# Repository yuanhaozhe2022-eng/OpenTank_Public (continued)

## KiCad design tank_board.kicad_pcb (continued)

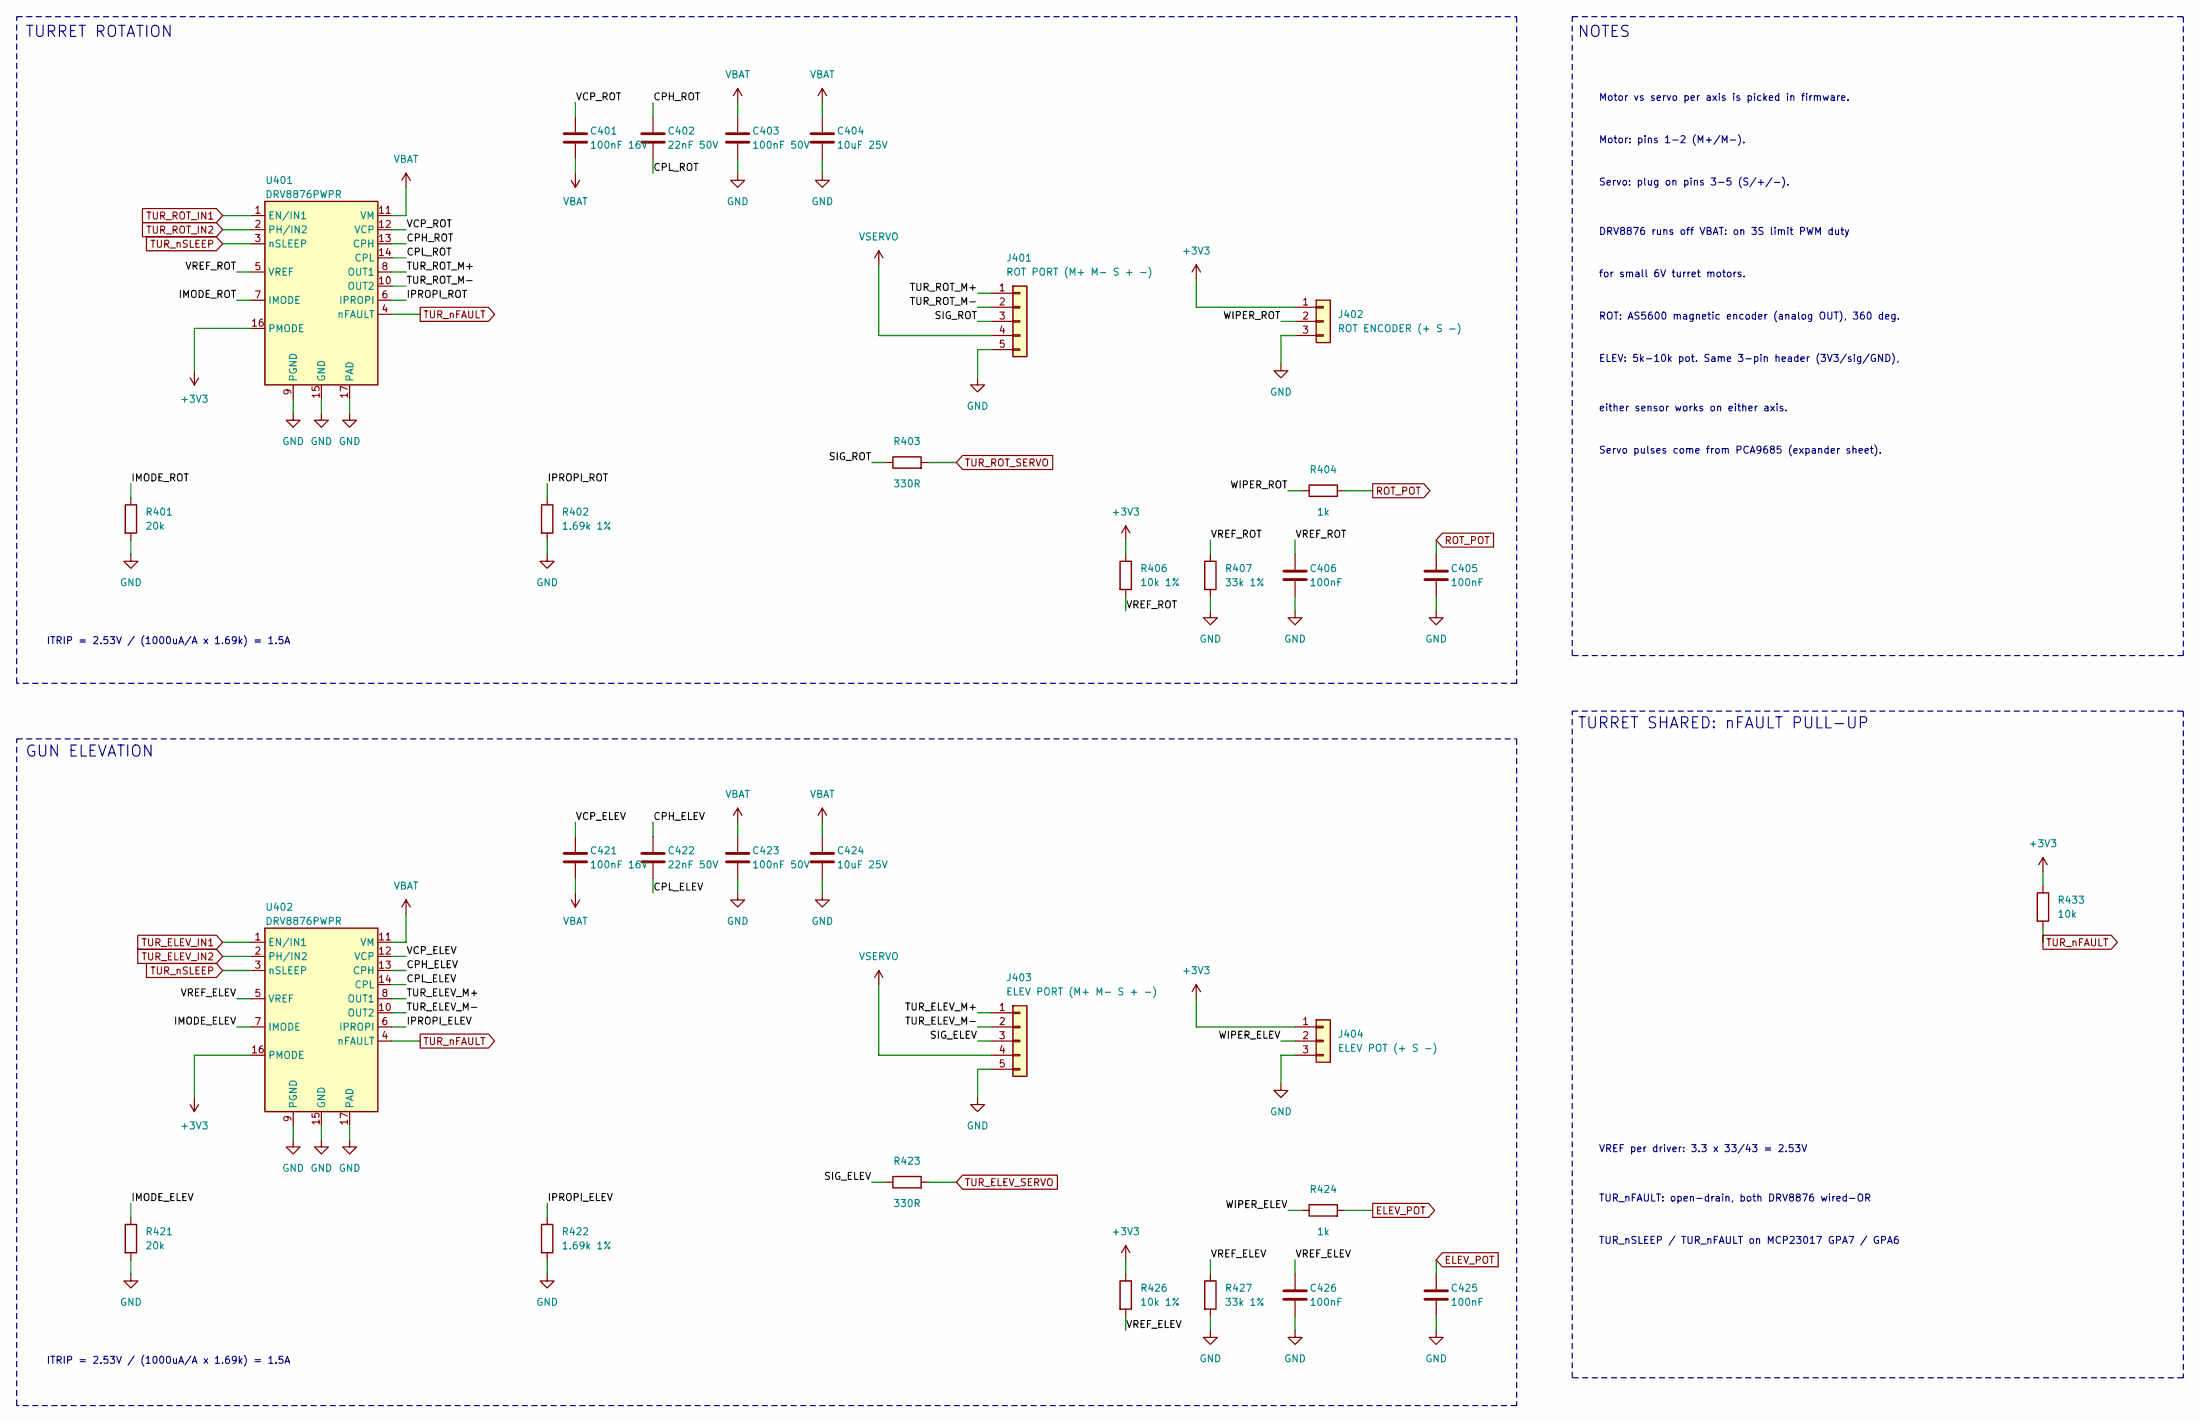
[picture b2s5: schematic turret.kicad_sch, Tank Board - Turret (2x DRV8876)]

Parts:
C401, C421: 100nF 16V; C_0603_1608Metric
C402, C422: 22nF 50V; C_0603_1608Metric
C403, C423: 100nF 50V; C_0603_1608Metric
C404, C424: 10uF 25V; C_1206_3216Metric
C405, C406, C425, C426: 100nF; C_0603_1608Metric
J401: ROT PORT (M+ M- S + -); PinHeader_1x05_P2.54mm_Vertical
J402: ROT ENCODER (+ S -); PinHeader_1x03_P2.54mm_Vertical
J403: ELEV PORT (M+ M- S + -); PinHeader_1x05_P2.54mm_Vertical
J404: ELEV POT (+ S -); PinHeader_1x03_P2.54mm_Vertical
R401, R421: 20k; R_0603_1608Metric
R402, R422: 1.69k 1%; R_0603_1608Metric
R403, R423: 330R; R_0603_1608Metric
R404, R424: 1k; R_0603_1608Metric
R406, R426: 10k 1%; R_0603_1608Metric
R407, R427: 33k 1%; R_0603_1608Metric
R433: 10k; R_0603_1608Metric
U401, U402: DRV8876PWPR; DRV887x_HTSSOP-16_PWP0016J_ThermalVias; MPN DRV8876PWPR

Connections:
+3V3: J402.1, J404.1, R406.1, R426.1, R433.1, U401.16 (PMODE), U402.16 (PMODE); also elsewhere on the board
/Turret/CPH_ELEV: C422.1, U402.13 (CPH)
/Turret/CPH_ROT: C402.1, U401.13 (CPH)
/Turret/CPL_ELEV: C422.2, U402.14 (CPL)
/Turret/CPL_ROT: C402.2, U401.14 (CPL)
/Turret/IMODE_ELEV: R421.1, U402.7 (IMODE)
/Turret/IMODE_ROT: R401.1, U401.7 (IMODE)
/Turret/IPROPI_ELEV: R422.1, U402.6 (IPROPI)
/Turret/IPROPI_ROT: R402.1, U401.6 (IPROPI)
/Turret/SIG_ELEV: J403.3, R423.1
/Turret/SIG_ROT: J401.3, R403.1
/Turret/TUR_ELEV_M+: J403.1, U402.8 (OUT1)
/Turret/TUR_ELEV_M-: J403.2, U402.10 (OUT2)
/Turret/TUR_ROT_M+: J401.1, U401.8 (OUT1)
/Turret/TUR_ROT_M-: J401.2, U401.10 (OUT2)
/Turret/VCP_ELEV: C421.1, U402.12 (VCP)
/Turret/VCP_ROT: C401.1, U401.12 (VCP)
/Turret/VREF_ELEV: C426.1, R426.2, R427.1, U402.5 (VREF)
/Turret/VREF_ROT: C406.1, R406.2, R407.1, U401.5 (VREF)
/Turret/WIPER_ELEV: J404.2, R424.1
/Turret/WIPER_ROT: J402.2, R404.1
ELEV_POT: C425.1, R424.2; also elsewhere on the board
GND: C403.2, C404.2, C405.2, C406.2, C423.2, C424.2, C425.2, C426.2, J401.5, J402.3, J403.5, J404.3, R401.2, R402.2, R407.2, R421.2, R422.2, R427.2, U401.9 (PGND), U401.15 (GND), U401.17 (PAD), U402.9 (PGND), U402.15 (GND), U402.17 (PAD); also elsewhere on the board
ROT_POT: C405.1, R404.2; also elsewhere on the board
TUR_ELEV_IN1: U402.1 (EN/IN1); also elsewhere on the board
TUR_ELEV_IN2: U402.2 (PH/IN2); also elsewhere on the board
TUR_ELEV_SERVO: R423.2; also elsewhere on the board
TUR_ROT_IN1: U401.1 (EN/IN1); also elsewhere on the board
TUR_ROT_IN2: U401.2 (PH/IN2); also elsewhere on the board
TUR_ROT_SERVO: R403.2; also elsewhere on the board
TUR_nFAULT: R433.2, U401.4 (nFAULT), U402.4 (nFAULT); also elsewhere on the board
TUR_nSLEEP: U401.3 (nSLEEP), U402.3 (nSLEEP); also elsewhere on the board
VBAT: C401.2, C403.1, C404.1, C421.2, C423.1, C424.1, U401.11 (VM), U402.11 (VM); also elsewhere on the board
VSERVO: J401.4, J403.4; also elsewhere on the board

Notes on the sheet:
TURRET ROTATION
ITRIP = 2.53V / (1000uA/A x 1.69k) = 1.5A
GUN ELEVATION
TURRET SHARED: nFAULT PULL-UP
VREF per driver: 3.3 x 33/43 = 2.53V
TUR_nFAULT: open-drain, both DRV8876 wired-OR
TUR_nSLEEP / TUR_nFAULT on MCP23017 GPA7 / GPA6
NOTES
Motor vs servo per axis is picked in firmware.
Motor: pins 1-2 (M+/M-).
Servo: plug on pins 3-5 (S/+/-).
DRV8876 runs off VBAT: on 3S limit PWM duty
for small 6V turret motors.
ROT: AS5600 magnetic encoder (analog OUT), 360 deg.
ELEV: 5k-10k pot. Same 3-pin header (3V3/sig/GND),
either sensor works on either axis.
Servo pulses come from PCA9685 (expander sheet).

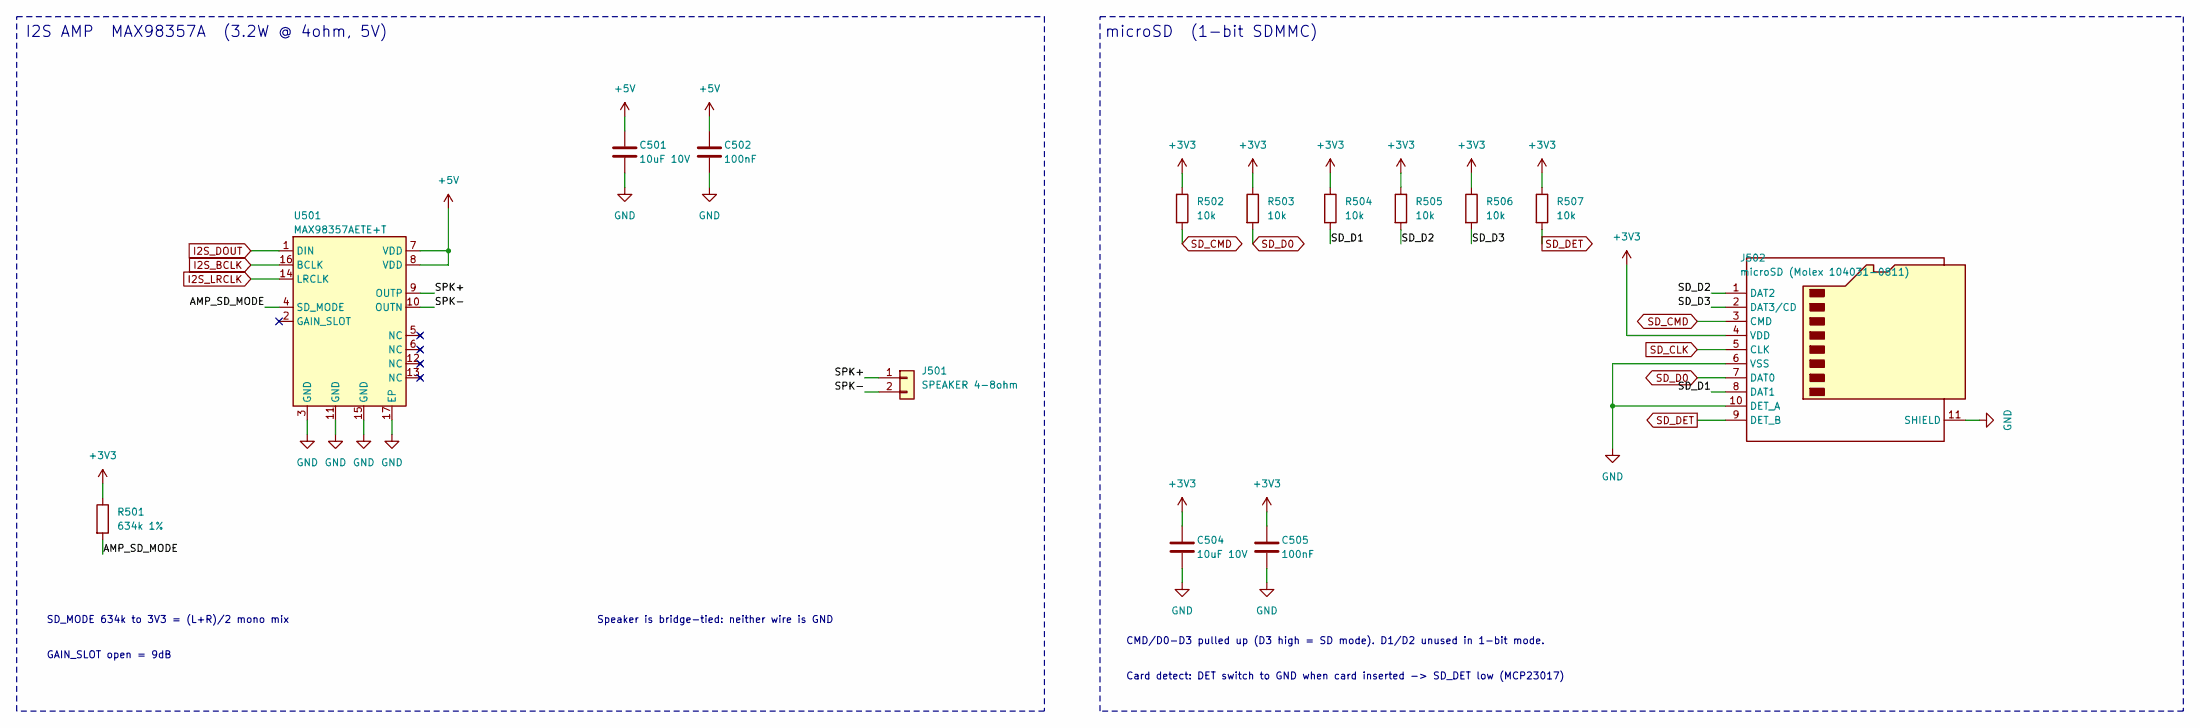
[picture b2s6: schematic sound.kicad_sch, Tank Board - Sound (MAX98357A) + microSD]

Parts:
C501, C504: 10uF 10V; C_0805_2012Metric
C502, C505: 100nF; C_0603_1608Metric
J501: SPEAKER 4-8ohm; JST_PH_B2B-PH-K_1x02_P2.00mm_Vertical; MPN JST B2B-PH-K-S
J502: microSD (Molex 104031-0811); microSD_HC_Molex_104031-0811; MPN Molex 104031-0811
R501: 634k 1%; R_0603_1608Metric
R502, R503, R504, R505, R506, R507: 10k; R_0603_1608Metric
U501: MAX98357AETE+T; TQFN-16-1EP_3x3mm_P0.5mm_EP1.23x1.23mm_ThermalVias; MPN MAX98357AETE+T

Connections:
+3V3: C504.1, C505.1, J502.4 (VDD), R501.1, R502.1, R503.1, R504.1, R505.1, R506.1, R507.1; also elsewhere on the board
+5V: C501.1, C502.1, U501.7 (VDD), U501.8 (VDD); also elsewhere on the board
/Sound_SD/AMP_SD_MODE: R501.2, U501.4 (SD_MODE)
/Sound_SD/SD_D1: J502.8 (DAT1), R504.2
/Sound_SD/SD_D2: J502.1 (DAT2), R505.2
/Sound_SD/SD_D3: J502.2 (DAT3/CD), R506.2
/Sound_SD/SPK+: J501.1, U501.9 (OUTP)
/Sound_SD/SPK-: J501.2, U501.10 (OUTN)
GND: C501.2, C502.2, C504.2, C505.2, J502.6 (VSS), J502.10 (DET_A), J502.11 (SHIELD), U501.3 (GND), U501.11 (GND), U501.15 (GND), U501.17 (EP); also elsewhere on the board
I2S_BCLK: U501.16 (BCLK); also elsewhere on the board
I2S_DOUT: U501.1 (DIN); also elsewhere on the board
I2S_LRCLK: U501.14 (LRCLK); also elsewhere on the board
SD_CLK: J502.5 (CLK); also elsewhere on the board
SD_CMD: J502.3 (CMD), R502.2; also elsewhere on the board
SD_D0: J502.7 (DAT0), R503.2; also elsewhere on the board
SD_DET: J502.9 (DET_B), R507.2; also elsewhere on the board

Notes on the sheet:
I2S AMP MAX98357A (3.2W @ 4ohm, 5V)
SD_MODE 634k to 3V3 = (L+R)/2 mono mix
GAIN_SLOT open = 9dB
Speaker is bridge-tied: neither wire is GND
microSD (1-bit SDMMC)
CMD/D0-D3 pulled up (D3 high = SD mode). D1/D2 unused in 1-bit mode.
Card detect: DET switch to GND when card inserted -> SD_DET low (MCP23017)

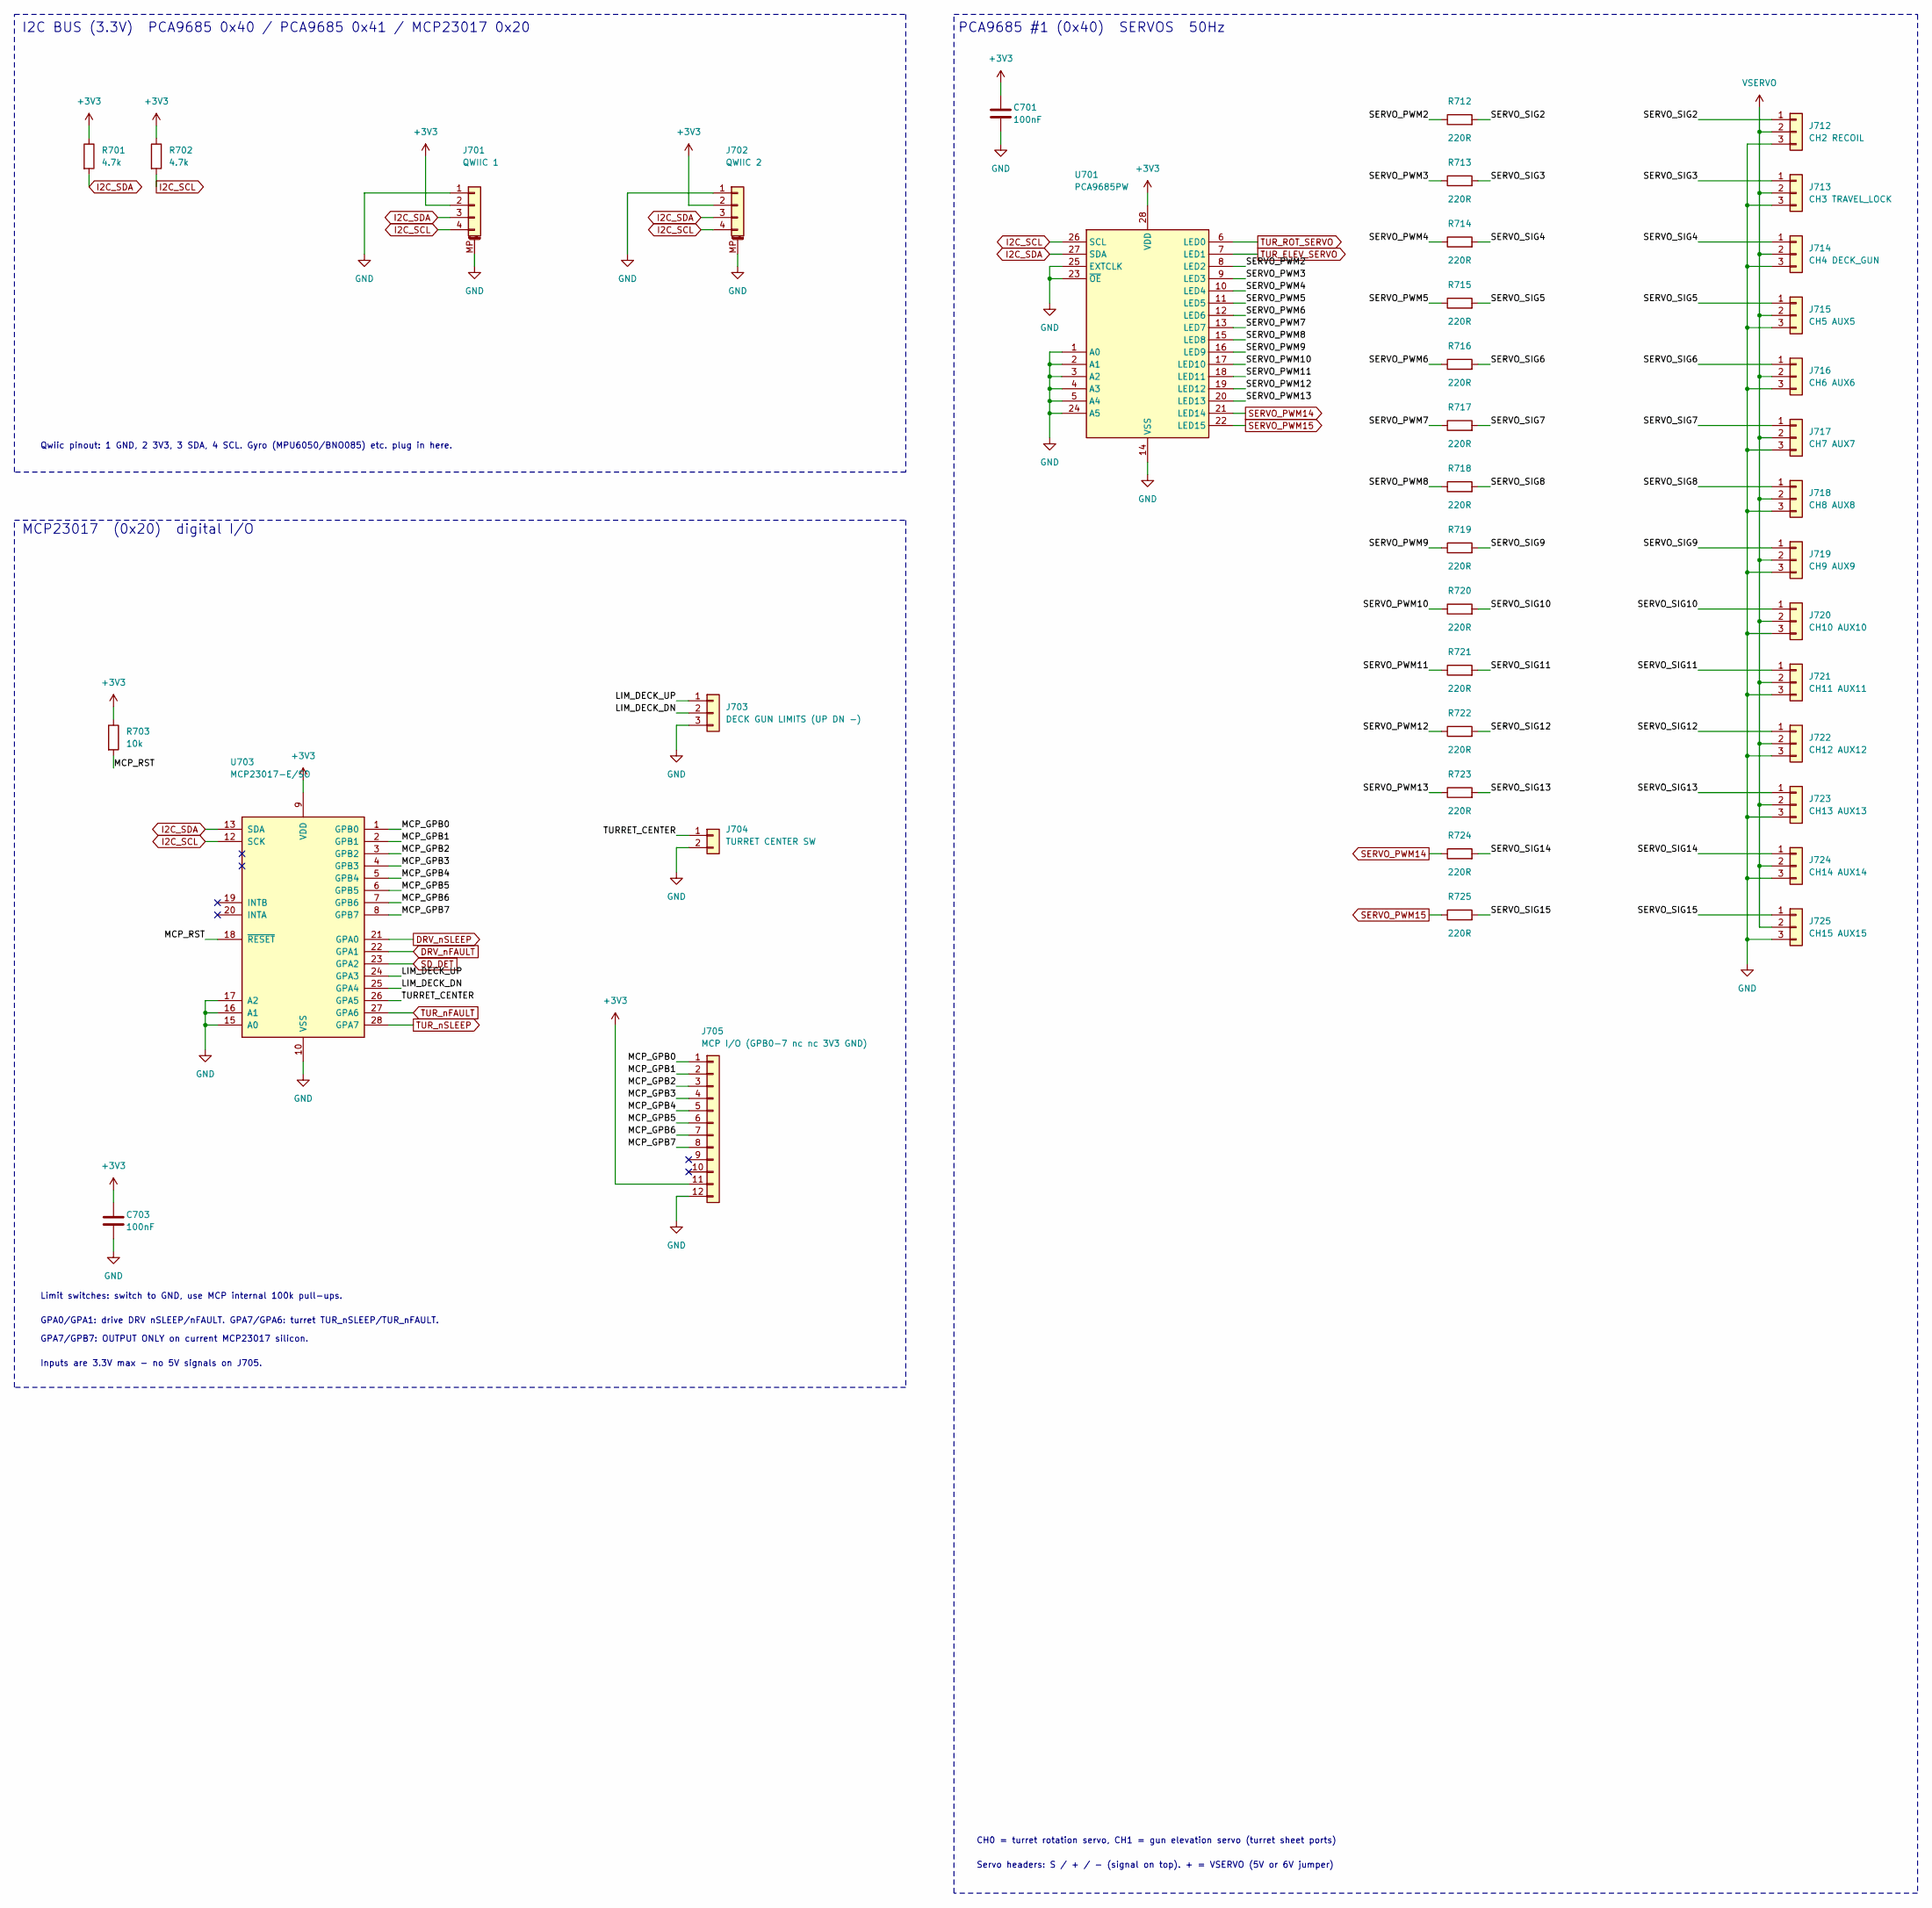
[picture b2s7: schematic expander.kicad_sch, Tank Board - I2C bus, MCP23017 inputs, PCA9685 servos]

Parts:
C701, C703: 100nF; C_0603_1608Metric
J701: QWIIC 1; JST_SH_SM04B-SRSS-TB_1x04-1MP_P1.00mm_Horizontal; MPN JST SM04B-SRSS-TB
J702: QWIIC 2; JST_SH_SM04B-SRSS-TB_1x04-1MP_P1.00mm_Horizontal; MPN JST SM04B-SRSS-TB
J703: DECK GUN LIMITS (UP DN -); PinHeader_1x03_P2.54mm_Vertical
J704: TURRET CENTER SW; PinHeader_1x02_P2.54mm_Vertical
J705: MCP I/O (GPB0-7 nc nc 3V3 GND); PinHeader_2x06_P2.54mm_Vertical
J712: CH2 RECOIL; PinHeader_1x03_P2.54mm_Vertical
J713: CH3 TRAVEL_LOCK; PinHeader_1x03_P2.54mm_Vertical
J714: CH4 DECK_GUN; PinHeader_1x03_P2.54mm_Vertical
J715: CH5 AUX5; PinHeader_1x03_P2.54mm_Vertical
J716: CH6 AUX6; PinHeader_1x03_P2.54mm_Vertical
J717: CH7 AUX7; PinHeader_1x03_P2.54mm_Vertical
J718: CH8 AUX8; PinHeader_1x03_P2.54mm_Vertical
J719: CH9 AUX9; PinHeader_1x03_P2.54mm_Vertical
J720: CH10 AUX10; PinHeader_1x03_P2.54mm_Vertical
J721: CH11 AUX11; PinHeader_1x03_P2.54mm_Vertical
J722: CH12 AUX12; PinHeader_1x03_P2.54mm_Vertical
J723: CH13 AUX13; PinHeader_1x03_P2.54mm_Vertical
J724: CH14 AUX14; PinHeader_1x03_P2.54mm_Vertical
J725: CH15 AUX15; PinHeader_1x03_P2.54mm_Vertical
R701, R702: 4.7k; R_0603_1608Metric
R703: 10k; R_0603_1608Metric
R712, R713, R714, R715, R716, R717, R718, R719, R720, R721, R722, R723, R724, R725: 220R; R_0603_1608Metric
U701: PCA9685PW; TSSOP-28_4.4x9.7mm_P0.65mm; MPN PCA9685PW,118
U703: MCP23017-E/SO; SOIC-28W_7.5x17.9mm_P1.27mm; MPN MCP23017-E/SO

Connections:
+3V3: C701.1, C703.1, J701.2, J702.2, J705.11, R701.1, R702.1, R703.1, U701.28 (VDD), U703.9 (VDD); also elsewhere on the board
/Expanders/LIM_DECK_DN: J703.2, U703.25 (GPA4)
/Expanders/LIM_DECK_UP: J703.1, U703.24 (GPA3)
/Expanders/MCP_GPB0: J705.1, U703.1 (GPB0)
/Expanders/MCP_GPB1: J705.2, U703.2 (GPB1)
/Expanders/MCP_GPB2: J705.3, U703.3 (GPB2)
/Expanders/MCP_GPB3: J705.4, U703.4 (GPB3)
/Expanders/MCP_GPB4: J705.5, U703.5 (GPB4)
/Expanders/MCP_GPB5: J705.6, U703.6 (GPB5)
/Expanders/MCP_GPB6: J705.7, U703.7 (GPB6)
/Expanders/MCP_GPB7: J705.8, U703.8 (GPB7)
/Expanders/MCP_RST: R703.2, U703.18 (~RESET)
/Expanders/SERVO_PWM2: R712.1, U701.8 (LED2)
/Expanders/SERVO_PWM3: R713.1, U701.9 (LED3)
/Expanders/SERVO_PWM4: R714.1, U701.10 (LED4)
/Expanders/SERVO_PWM5: R715.1, U701.11 (LED5)
/Expanders/SERVO_PWM6: R716.1, U701.12 (LED6)
/Expanders/SERVO_PWM7: R717.1, U701.13 (LED7)
/Expanders/SERVO_PWM8: R718.1, U701.15 (LED8)
/Expanders/SERVO_PWM9: R719.1, U701.16 (LED9)
/Expanders/SERVO_PWM10: R720.1, U701.17 (LED10)
/Expanders/SERVO_PWM11: R721.1, U701.18 (LED11)
/Expanders/SERVO_PWM12: R722.1, U701.19 (LED12)
/Expanders/SERVO_PWM13: R723.1, U701.20 (LED13)
/Expanders/SERVO_SIG2: J712.1, R712.2
/Expanders/SERVO_SIG3: J713.1, R713.2
/Expanders/SERVO_SIG4: J714.1, R714.2
/Expanders/SERVO_SIG5: J715.1, R715.2
/Expanders/SERVO_SIG6: J716.1, R716.2
/Expanders/SERVO_SIG7: J717.1, R717.2
/Expanders/SERVO_SIG8: J718.1, R718.2
/Expanders/SERVO_SIG9: J719.1, R719.2
/Expanders/SERVO_SIG10: J720.1, R720.2
/Expanders/SERVO_SIG11: J721.1, R721.2
/Expanders/SERVO_SIG12: J722.1, R722.2
/Expanders/SERVO_SIG13: J723.1, R723.2
/Expanders/SERVO_SIG14: J724.1, R724.2
/Expanders/SERVO_SIG15: J725.1, R725.2
/Expanders/TURRET_CENTER: J704.1, U703.26 (GPA5)
DRV_nFAULT: U703.22 (GPA1); also elsewhere on the board
DRV_nSLEEP: U703.21 (GPA0); also elsewhere on the board
GND: C701.2, C703.2, J701.1, J701.MP (MountPin), J702.1, J702.MP (MountPin), J703.3, J704.2, J705.12, J712.3, J713.3, J714.3, J715.3, J716.3, J717.3, J718.3, J719.3, J720.3, J721.3, J722.3, J723.3, J724.3, J725.3, U701.1 (A0), U701.2 (A1), U701.3 (A2), U701.4 (A3), U701.5 (A4), U701.14 (VSS), U701.23 (~OE), U701.24 (A5), U701.25 (EXTCLK), U703.10 (VSS), U703.15 (A0), U703.16 (A1), U703.17 (A2); also elsewhere on the board
I2C_SCL: J701.4, J702.4, R702.2, U701.26 (SCL), U703.12 (SCK); also elsewhere on the board
I2C_SDA: J701.3, J702.3, R701.2, U701.27 (SDA), U703.13 (SDA); also elsewhere on the board
SD_DET: U703.23 (GPA2); also elsewhere on the board
SERVO_PWM14: R724.1, U701.21 (LED14); also elsewhere on the board
SERVO_PWM15: R725.1, U701.22 (LED15); also elsewhere on the board
TUR_ELEV_SERVO: U701.7 (LED1); also elsewhere on the board
TUR_ROT_SERVO: U701.6 (LED0); also elsewhere on the board
TUR_nFAULT: U703.27 (GPA6); also elsewhere on the board
TUR_nSLEEP: U703.28 (GPA7); also elsewhere on the board
VSERVO: J712.2, J713.2, J714.2, J715.2, J716.2, J717.2, J718.2, J719.2, J720.2, J721.2, J722.2, J723.2, J724.2, J725.2; also elsewhere on the board

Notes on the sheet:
I2C BUS (3.3V) PCA9685 0x40 / PCA9685 0x41 / MCP23017 0x20
Qwiic pinout: 1 GND, 2 3V3, 3 SDA, 4 SCL. Gyro (MPU6050/BNO085) etc. plug in here.
MCP23017 (0x20) digital I/O
Limit switches: switch to GND, use MCP internal 100k pull-ups.
GPA0/GPA1: drive DRV nSLEEP/nFAULT. GPA7/GPA6: turret TUR_nSLEEP/TUR_nFAULT.
GPA7/GPB7: OUTPUT ONLY on current MCP23017 silicon.
Inputs are 3.3V max - no 5V signals on J705.
PCA9685 #1 (0x40) SERVOS 50Hz
Servo headers: S / + / - (signal on top). + = VSERVO (5V or 6V jumper)
CH0 = turret rotation servo, CH1 = gun elevation servo (turret sheet ports)
